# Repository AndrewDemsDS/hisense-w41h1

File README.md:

# Hisense AEH-W41H1: local A/C control with ESPHome

ESPHome firmware that takes the place of the ConnectLife cloud on a Hisense A/C with an
`AEH-W41H1` Wi-Fi module. It speaks the A/C's internal RS-485 bus and presents the unit to Home
Assistant as a native climate device, with no cloud.

> Not affiliated with, endorsed by, or supported by Hisense, Realtek or ESPHome. See
> [`NOTICE.md`](NOTICE.md). Reverse engineering of hardware you own, for interoperability. Do this
> at your own risk: a bad flash can brick the stock module (recoverable with a dump you took
> first).

**Documentation: [andrewdemsds.github.io/hisense-w41h1](https://andrewdemsds.github.io/hisense-w41h1/).**
The site is generated from [`docs/guide/`](docs/guide/), [`firmware/docs/`](firmware/docs/) and
[`reverse-engineering/docs/`](reverse-engineering/docs/). This README only points into it.

```
Home Assistant ── ESPHome native API over Wi-Fi ──► ESP32 board or stock module
                                                    (hisense_ac ESPHome component)
                                                           │ RS-485 (9600 8N1)
                                                           ▼
                                                    A/C mainboard
```

## What you get

- A climate entity in Home Assistant over the ESPHome API: mode (including auto), setpoint
  (16 to 32 °C), six fan settings, vertical swing, and Eco, Quiet, Turbo and Sleep as presets.
- Switches for the special modes, the panel display and the command beeper.
- Commands that are checked: the node compares each one with the unit's status and sends it
  again when the unit missed it.
- Temperatures, compressor frequency, a power and energy estimate, and bus diagnostics.
- Updates over Wi-Fi with ESPHome's own OTA.

What each entity is and its limits: [Everyday Control](docs/guide/Everyday-Control.md).

## Which hardware

One firmware, three kinds of hardware.

| Hardware | State |
|---|---|
| An ESP32 board (ESP32-C3 SuperMini or classic ESP32) with a 3.3 V RS-485 transceiver, in place of the module | recommended. On live units since 2026-08 |
| The stock module itself (Realtek RTL8710C), through ESPHome's LibreTiny platform | one module in an A/C since 2026-10-10. No rollback, and a SOIC-8 clip is the only recovery |
| Other ESPHome chips (ESP8266, RP2040) | example configs that compile. Never run |

The [User Guide](docs/guide/User-Guide.md) compares them and says which page to read next.

## The quickest path to a working unit

With an ESP32 board wired as in
[ESP32 Replacement Board](docs/guide/ESP32-Replacement-Build.md), and ESPHome 2026.10.2 installed
(`pipx install esphome==2026.10.2`):

```
git clone https://github.com/AndrewDemsDS/hisense-w41h1.git
cd hisense-w41h1/firmware/esphome
cp secrets.yaml.example secrets.yaml      # then fill in Wi-Fi, a hotspot password and an API key
esphome run w41h1-esp32c3.yaml            # ESP32-C3 SuperMini. Classic ESP32: w41h1.yaml
```

Home Assistant then discovers the node, and you adopt it with the API key. Do not wire a freshly
flashed board straight into the A/C: the guide brings it up in three stages. For local builds and
the bench there is a wrapper script, `python3 firmware/scripts/dev.py`
([Build, Flash and Test](docs/guide/Build-Flash-Test.md)).

> **Stock module: dump it first.** The only complete way back to what a module had on it is a
> whole-chip write, with a CH341A and a clip, of a dump taken before the first flash.

## Where everything is

| I want to | Read |
|---|---|
| choose the hardware and follow the route | [User Guide](docs/guide/User-Guide.md) |
| know the module and the 4-pin port | [Hardware and Wiring](docs/guide/Hardware-and-Wiring.md) |
| install the tools and fill in the secrets | [Build Environment](docs/guide/ESP32-Build-Environment.md) |
| add the node to Home Assistant, update it, pin a release | [ESPHome Firmware](docs/guide/ESPHome-Build.md) |
| run ESPHome on the stock module | [The Stock Module](docs/guide/Stock-Module-Build.md) |
| see every entity and read the diagnostics | [Entities and Diagnostics](docs/guide/Entities-and-Diagnostics.md) |
| fix something | [Troubleshooting and FAQ](docs/guide/FAQ-Gotchas.md), [Recovery and Reflash](docs/guide/Recovery-and-Reflash.md) |
| find my way around the code and the tests | [Repo Map and Build Pipeline](docs/guide/Repo-Map-and-Build-Pipeline.md), [Testing and QA](docs/guide/Testing-and-QA.md) |
| read the protocol | [`reverse-engineering/docs/03-rs485-ac-protocol.md`](reverse-engineering/docs/03-rs485-ac-protocol.md) |
| contribute, or report a security problem | [`CONTRIBUTING.md`](CONTRIBUTING.md), [`SECURITY.md`](SECURITY.md) |
| see what changed | [`CHANGELOG.md`](CHANGELOG.md) |

Once local control works, you can block the vendor module's way out to the internet:
[`reverse-engineering/docs/04-cloud-and-firewall.md`](reverse-engineering/docs/04-cloud-and-firewall.md).

## Matter firmware (retired)

Until 2026-10-12 this repository also shipped two Matter firmwares. Both are retired. The last
tree that has them is the signed tag
[`matter-final`](https://github.com/AndrewDemsDS/hisense-w41h1/tree/matter-final). A unit that
runs one keeps working and can be moved to ESPHome over the air:
[Matter Firmware (Retired)](docs/guide/Matter-Firmware-Retired.md).

## AI assistance

I built this with AI assistance across the code, reverse-engineering, and docs. Commits carry an
`Assisted-by: AI` trailer.

## License

Original code and docs: **MIT** ([`LICENSE`](LICENSE)). Third-party tools the build fetches and
what was adapted from them: [`NOTICE.md`](NOTICE.md).

Credits: the protocol work started from
[`pslawinski/esphome_airconintl`](https://github.com/pslawinski/esphome_airconintl) and
[`deiger/AirCon`](https://github.com/deiger/AirCon). What came from each is in
[`NOTICE.md`](NOTICE.md#acknowledgements-earlier-work-on-this-ac-bus).

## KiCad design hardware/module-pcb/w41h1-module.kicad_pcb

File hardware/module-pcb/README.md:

# Replacement module PCB

> **Rev C has not been fabricated.** Rev B was: five assembled boards from JLCPCB, ordered
> 2026-10-28, and one of them has run on an A/C unit since 2026-11-06 (bus link up, OTA works).
> Rev C is still a test board for the A/C units, not a fit for the stock module's bay: the bay's
> size is unmeasured, and the A/C header's dimensions are marked VERIFY below.

A test board for local control of the A/C: an ESP32-C3 module, a 3.3 V RS-485 transceiver and
the 4-pin A/C connector. It runs the same ESPHome firmware as the hand-wired ESP32-C3 build,
with the same pins, so `firmware/esphome/w41h1-esp32c3.yaml` applies unchanged. The matching
case is in [`../module-case`](../module-case).

## Rev C

Two things came out of putting a rev B board on a unit:

- No plug that fits the JST PH header matched the A/C's lead. The lead plugs into the stock
  module's own header, so rev C takes that header: `J1` is the 4-pin 2.0 mm side-entry
  header desoldered from the stock module (measured on 2026-11-06: 2.0 mm pitch, no plastic
  pegs), on a project footprint written by `scripts/place.py`. Its mating face sits on the board
  edge. How far the pin row sits behind that face (`J1_PIN_INSET`, 4.0 mm), the drill (0.9 mm)
  and the body size are placeholders marked `VERIFY` in `place.py` until they are measured on
  the stock module.
- The programming pads were awkward to use. `J2` is now a 2.54 mm pin header on the top side,
  so a standard jumper lead fits. The 1.27 mm pads on the bottom are gone, and the USB test pads
  stay.

Neither connector is assembled: both are marked not fitted, left out of the BOM and placement
files, and soldered in by hand. The board grew from 52 to 56 mm to make room for the header.
`place.py` also swaps the footprints on the board to match the schematic, so a footprint
change needs no step in the GUI.

Rev A was the size of the stock PCB (40 x 20.5 mm, estimated from the FCC photos) with parts on
both sides. Rev B traded the stock size for a lower assembly price: every assembled part is on
the top side.

## What is on it

| Block | Part | Notes |
|---|---|---|
| MCU | ESP32-C3-WROOM-02 | PCB antenna at the end away from the connector, over bare board |
| Supply | TLV62569DBV buck, 2.2 uH, 5 V to 3.3 V | the A/C port is rated 5 V at 450 mA, and a buck draws less from it than a linear regulator during Wi-Fi bursts |
| Bus | SP3485EN, SM712 TVS on A and B | DE and RE tied to one GPIO, 10 k pulldown on DE, 10 k pullup on RO |
| A/C port | 4-pin, 2.0 mm, side entry (`J1`) | the stock module's own header, desoldered and soldered in by hand; not assembled |
| Status LED | 0603 on GPIO8, lights when the pin is low | same as the SuperMini's LED |
| Programming | `J2` 2.54 mm pin header on top (GND, 3V3, EN, IO9, TX, RX, pin 1 at the board edge) and USB D-, D+, 5 V, GND test pads on the bottom | the header is not assembled |

## Pins

| Signal | GPIO | Goes to |
|---|---|---|
| Bus TX | 5 | transceiver DI |
| Bus RX | 6 | transceiver RO |
| Bus DE | 10 | transceiver DE and RE |
| Status LED | 8 | LED cathode |
| Boot | 9 | `J2` pin 4, 10 k pullup |
| UART0 TX, RX | 21, 20 | `J2` pins 5 and 6 |
| USB D-, D+ | 18, 19 | `TP1`, `TP2` |

`J1` follows the pinout in [Hardware and Wiring](../../docs/guide/Hardware-and-Wiring.md): pin 1 is
5 V, pins 2 and 3 are the RS-485 pair, pin 4 is ground. A and B are interchangeable on this bus:
if the link does not come up, swap them in the lead.

## Dimensions

| Dimension | Value |
|---|---|
| Board | 56 x 22 mm, 2 layers, 1.6 mm |
| Mounting holes | two, 2.2 mm (M2), 2.7 mm in from the connector end and from each long edge |
| A/C header `J1` | 4-pin, 2.0 mm pitch (measured on the stock module), mating face on the board edge, pin row 4.0 mm behind it, 0.9 mm drills. Inset, drill and body size are VERIFY |
| Programming header `J2` | 1x6, 2.54 mm, top side, 0.9 mm drills |
| Smallest drill | 0.3 mm |

All of them are constants at the top of `scripts/place.py`. Change the numbers and run it again:
it writes the A/C header footprint, puts the footprints the schematic names on the board,
places every footprint, redraws the outline and the keepouts and refills the ground pours. Run
it with `--unroute` when a change moves parts, then route again.

`place.py` also edits the module footprint: of its 13 thermal vias of 0.2 mm, four become
0.3 mm and the rest plain copper, because anything under 0.3 mm costs extra at JLCPCB. KiCad
reports that change as one "footprint differs from library" warning.

## Ordering at JLCPCB

`bash scripts/fab.sh`, then on JLCPCB's quote page: upload the gerber zip, keep the minimum via
hole at 0.3 mm and the 4-wire Kelvin test off, turn on assembly as Economic, top side, then upload
`fab/w41h1-module-bom.csv` and `fab/w41h1-module-cpl.csv`. All 15 BOM lines match JLCPCB's
library. `J1` and `J2` are in neither file: solder them in yourself.

The quote on 2026-10-14 for five assembled rev B boards was EUR 51.99 before shipping:

| Item | EUR |
|---|---|
| Bare boards | 3.57 |
| Assembly setup and stencil | 8.72 |
| Parts | 20.82 |
| Extended parts fee (six parts outside JLCPCB's basic library) | 13.77 |
| Machine and hand assembly, nitrogen reflow | 5.11 |

Shipping by DHL was about EUR 21 more. Prices change, so quote again before ordering. Rev C
already leaves the connectors off the order; swapping the diode, the inductor and the 453 k
resistor for basic library parts would cut it further.

## Files

- `w41h1-module.kicad_pro`, `.kicad_sch`, `.kicad_pcb`: the KiCad 10 project.
- `fp-lib-table`, `w41h1.pretty/`: the project footprint library, holding the A/C header
  footprint that `place.py` writes.
- `bom.csv`: the bill of materials with manufacturer and LCSC part numbers.
- `scripts/place.py`: the A/C header footprint, footprint swaps, placement, outline, keepouts,
  silkscreen labels, ground pours and the pre-routed connections, all derived from the
  dimensions above.
- `scripts/route.py`: runs Freerouting on the board and cleans up after it (track widths,
  stray vias, pour refill).
- `scripts/stitch.py`: joins the ground pour islands with vias after routing.
- `scripts/fab.sh`: runs ERC and DRC, then writes the fabrication files into `fab/`.
- `scripts/jlc_cpl.py`: turns KiCad's placement file into JLCPCB's column names.

## Fabrication files

```bash
bash scripts/fab.sh
```

It stops if ERC or DRC reports an error. Otherwise `fab/` (not tracked in git) holds:

| File | For |
|---|---|
| `w41h1-module-gerbers.zip` | the board order: two layers, 1.6 mm |
| `w41h1-module-bom.csv`, `w41h1-module-cpl.csv` | assembly: parts and placement, top side, without the two connectors |
| `w41h1-module-schematic.pdf` | reading the circuit without KiCad |
| `w41h1-module.step` | the 3D model the case is checked against |

## Regenerating the layout

```bash
python3 scripts/place.py --unroute     # footprint, swaps, place, pre-route, pour
python3 scripts/route.py               # Freerouting (jar path in FREEROUTING_JAR), then cleanup
python3 scripts/stitch.py              # join the ground islands
bash scripts/fab.sh
```

The regulator's connections, the module's supply link and three boxed-in ground pads are
pre-routed by `place.py`. The autorouter does the rest, and it gives a different result on
every run, so check that DRC reports no unconnected items each time. `route.py` prints its own
count after the import; the pour islands it includes are what `stitch.py` joins. Freerouting
2.5 does not count the pre-routed connections as routed and logs them as "unrouted" at the end:
that is expected. Nothing is routed by hand.

## What was checked

- ERC: no violations.
- DRC with schematic parity: no errors and no unconnected items. Two warnings remain, the
  module's antenna outline on the silkscreen crossing the board edge, plus the field notes
  below.
- The BOM has 15 lines and the placement file 23 parts, none of them `J1` or `J2`.
- The case ([`../module-case`](../module-case)) against the board's STEP: no overlap. The STEP
  leaves out the two not-fitted connectors, so that check does not see them.
- Pinouts and external parts against the manufacturers' datasheets, for the TLV62569DBV
  (pin order, 0.6 V feedback reference, 10 to 47 uF output capacitance), the
  ESP32-C3-WROOM-02 (pin table, pullups on GPIO2, GPIO8 and GPIO9, 10 k and 1 uF on EN,
  0.5 A supply) and the SP3485 (pin order, 3.3 V supply). The divider of 453 k over 100 k
  gives 3.32 V.
- The SM712 against its datasheet: pins 1 and 2 are the two lines, pin 3 is ground, and it
  clamps the +12 V to -7 V range RS-485 uses.
- The inductor (`L1`, FTC252012S2R2MGCA) against the maker's catalogue: 2.2 uH, 65 mOhm
  maximum, 2.7 A heating current and 3.3 A saturation current at worst, well above what this
  board draws.
- SPICE runs of the feedback divider, the EN delay and the decoupling networks pass.
- The gerbers hold every layer and both drill files.

## Before ordering

- Check the placement preview on JLCPCB's order page, part by part: it stayed blank in the
  browser used for the quote above, so part orientations have not been checked there. The
  placement file passes KiCad's rotations through unchanged.
- Measure the stock header before ordering: the distance from its mating face to the pin row
  (`J1_PIN_INSET`), its pin size (`J1_DRILL`) and its body (`J1_BODY`) are placeholders in
  `scripts/place.py`. Also confirm that its pin 1 is 5 V.
- Apart from the pre-routed parts, the routing came from an autorouter (Freerouting 2.5.0)
  with the cleanup in `route.py` and nothing by hand. The tracks under the module on the
  bottom side are longer than a hand layout would make them, which is harmless at 9600 baud.
- `J1` and `J2` are marked as not fitted. Solder them in yourself.
- Schematic parity lists 30 notes about fields (part number, description) that the footprints
  on the board do not carry. "Update PCB from Schematic" in KiCad copies them over.

## First power-up

Follow the staged bring-up in the
[ESP32 replacement guide](../../docs/guide/ESP32-Replacement-Build.md): flash and test on the
bench first, then connect only A and B to the unit, and power the board from the A/C port
last. Erase the module's flash before the first flash. The `PROG` header is labelled on the
top: hold IO9 low while EN rises to enter the bootloader over UART0, or use the USB pads on
the bottom.

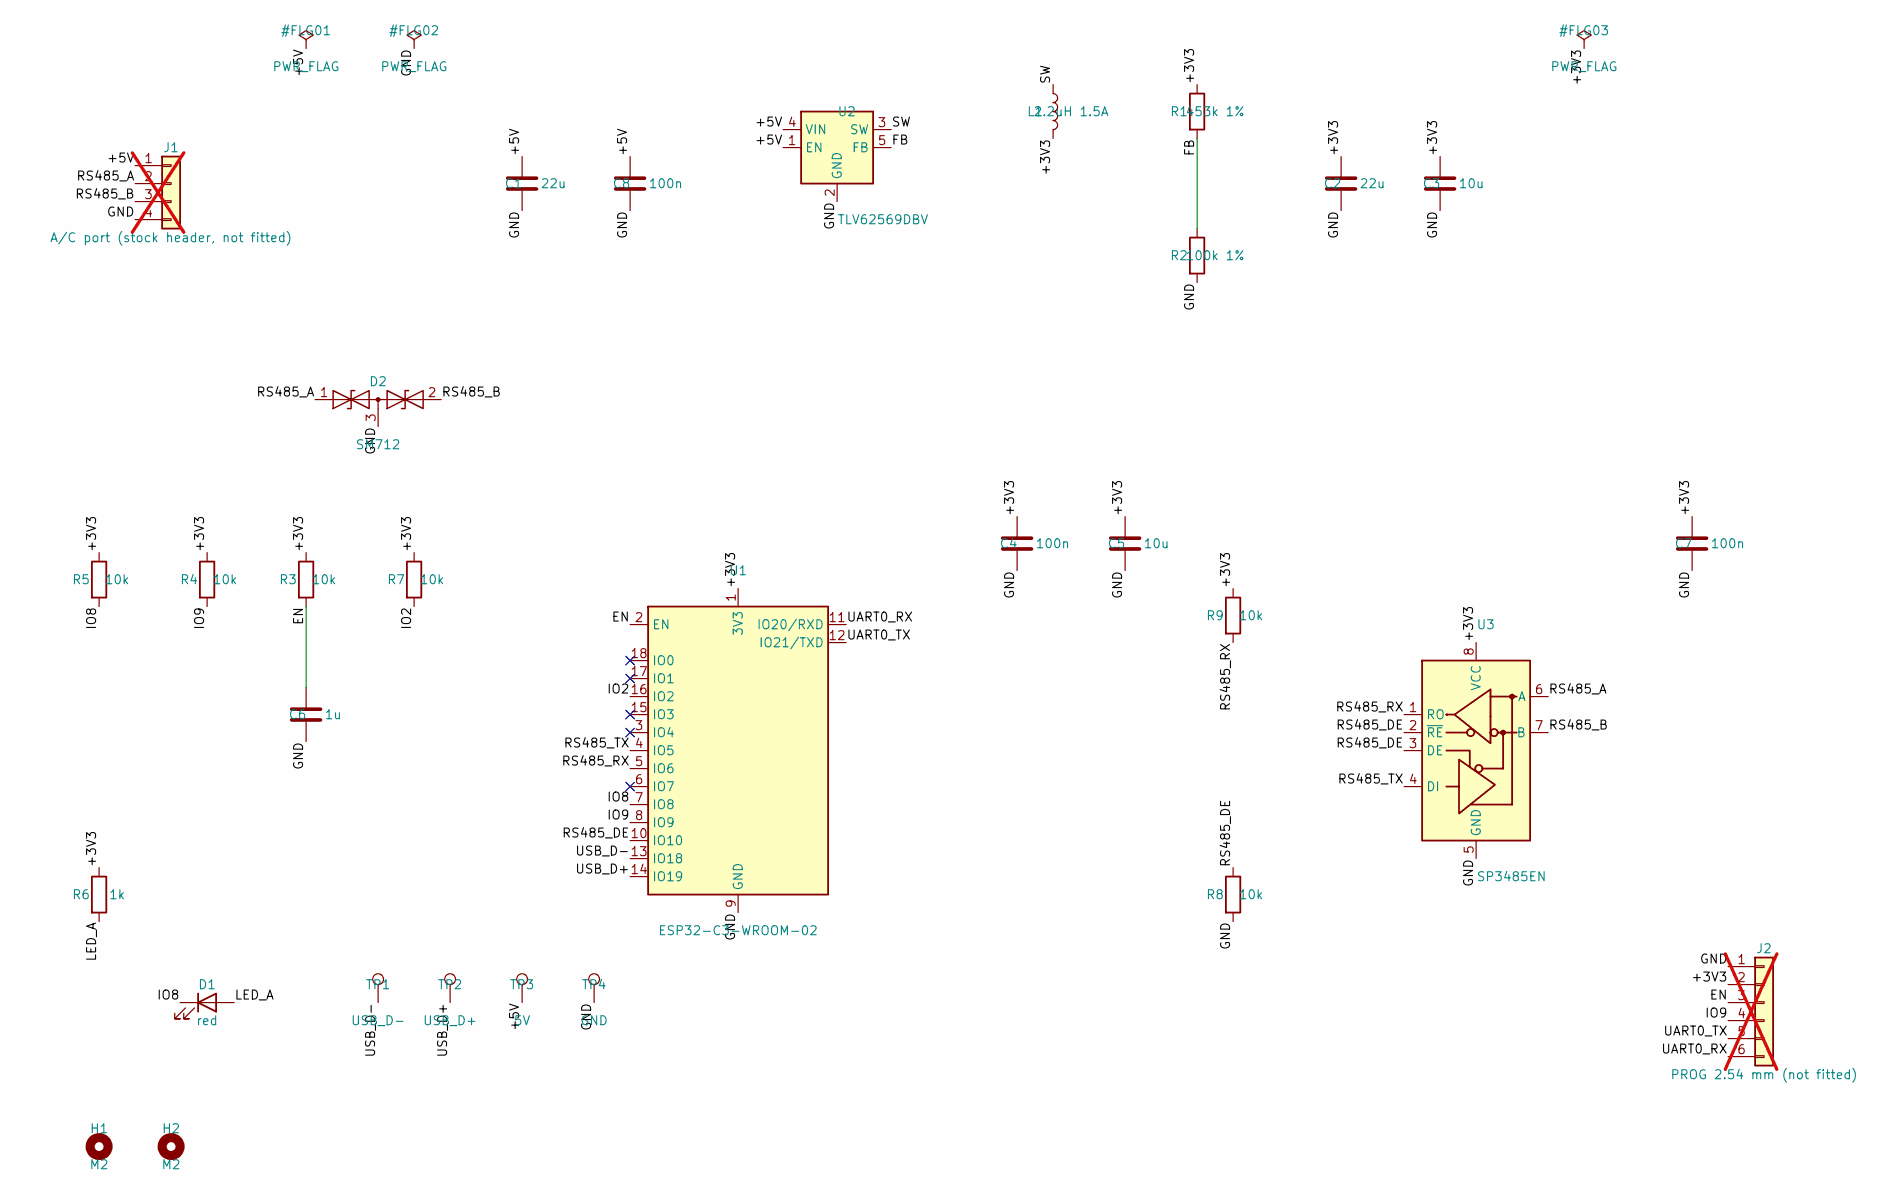
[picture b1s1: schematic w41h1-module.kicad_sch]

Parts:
C1, C2: 22u; C_0805_2012Metric; MPN CL21A226MAQNNNE; LCSC C45783
C3: 10u; C_0805_2012Metric; MPN CL21A106KAYNNNE; LCSC C15850
C4, C7, C8: 100n; C_0603_1608Metric; MPN CC0603KRX7R9BB104; LCSC C14663
C5: 10u; C_0603_1608Metric; MPN CL10A106KP8NNNC; LCSC C19702
C6: 1u; C_0603_1608Metric; MPN CL10A105KB8NNNC; LCSC C15849
D1: red; LED_0603_1608Metric; MPN KT-0603R; LCSC C2286
D2: SM712; SOT-23; MPN SM712; LCSC C502564
H1, H2: M2; MountingHole_2.2mm_M2
J1: A/C port (stock header, not fitted); AC_Header_1x04_P2.00mm_Horizontal; not fitted
J2: PROG 2.54 mm (not fitted); PinHeader_1x06_P2.54mm_Vertical; not fitted
L1: 2.2uH 1.5A; L_1008_2520Metric; MPN FTC252012S2R2MGCA; LCSC C48888311
R1: 453k 1%; R_0603_1608Metric; MPN 0603WAF4533T5E; LCSC C25818
R2: 100k 1%; R_0603_1608Metric; MPN 0603WAF1003T5E; LCSC C25803
R3, R4, R5, R7, R8, R9: 10k; R_0603_1608Metric; MPN 0603WAF1002T5E; LCSC C25804
R6: 1k; R_0603_1608Metric; MPN 0603WAF1001T5E; LCSC C21190
TP1: USB_D-; TestPoint_Pad_D1.0mm
TP2: USB_D+; TestPoint_Pad_D1.0mm
TP3: 5V; TestPoint_Pad_D1.0mm
TP4: GND; TestPoint_Pad_D1.0mm
U1: ESP32-C3-WROOM-02; MPN ESP32-C3-WROOM-02-N4; LCSC C2934560
U2: TLV62569DBV; SOT-23-5; MPN TLV62569DBVR; LCSC C141836
U3: SP3485EN; SOIC-8_3.9x4.9mm_P1.27mm; MPN SP3485EN-L/TR; LCSC C8963

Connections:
/+3V3: C2.1, C3.1, C4.1, C5.1, C7.1, J2.2, L1.2, R1.1, R3.1, R4.1, R5.1, R6.1, R7.1, R9.1, U1.1 (3V3), U3.8 (VCC)
/+5V: C1.1, C8.1, J1.1, TP3.1, U2.1 (EN), U2.4 (VIN)
/EN: C6.1, J2.3, R3.2, U1.2 (EN)
/FB: R1.2, R2.1, U2.5 (FB)
/GND: C1.2, C2.2, C3.2, C4.2, C5.2, C6.2, C7.2, C8.2, D2.3 (common), J1.4, J2.1, R2.2, R8.2, TP4.1, U1.9 (GND), U1.19 (GND), U2.2 (GND), U3.5 (GND)
/IO2: R7.2, U1.16 (IO2)
/IO8: D1.1 (K), R5.2, U1.7 (IO8)
/IO9: J2.4, R4.2, U1.8 (IO9)
/LED_A: D1.2 (A), R6.2
/RS485_A: D2.1 (A1), J1.2, U3.6 (A)
/RS485_B: D2.2 (A2), J1.3, U3.7 (B)
/RS485_DE: R8.1, U1.10 (IO10), U3.2 (~RE), U3.3 (DE)
/RS485_RX: R9.2, U1.5 (IO6), U3.1 (RO)
/RS485_TX: U1.4 (IO5), U3.4 (DI)
/SW: L1.1, U2.3 (SW)
/UART0_RX: J2.6, U1.11 (IO20/RXD)
/UART0_TX: J2.5, U1.12 (IO21/TXD)
/USB_D+: TP2.1, U1.14 (IO19)
/USB_D-: TP1.1, U1.13 (IO18)

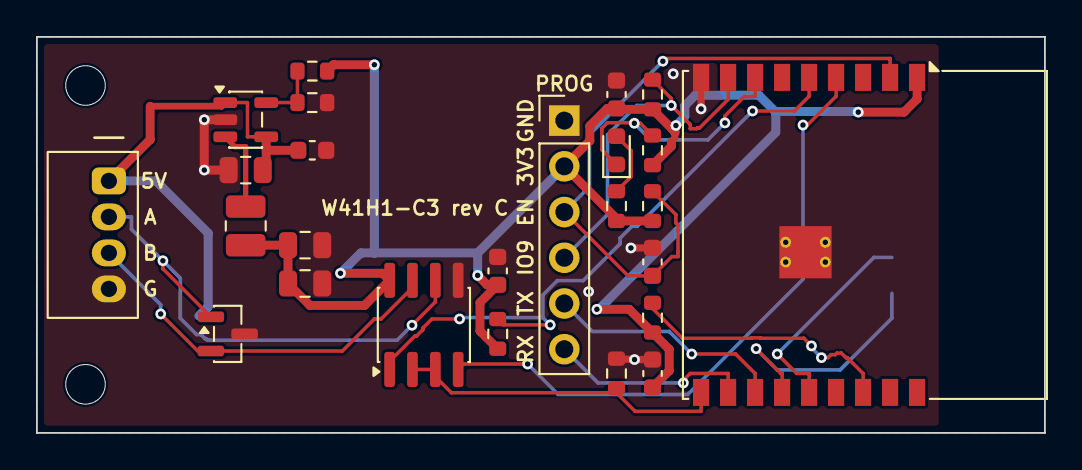
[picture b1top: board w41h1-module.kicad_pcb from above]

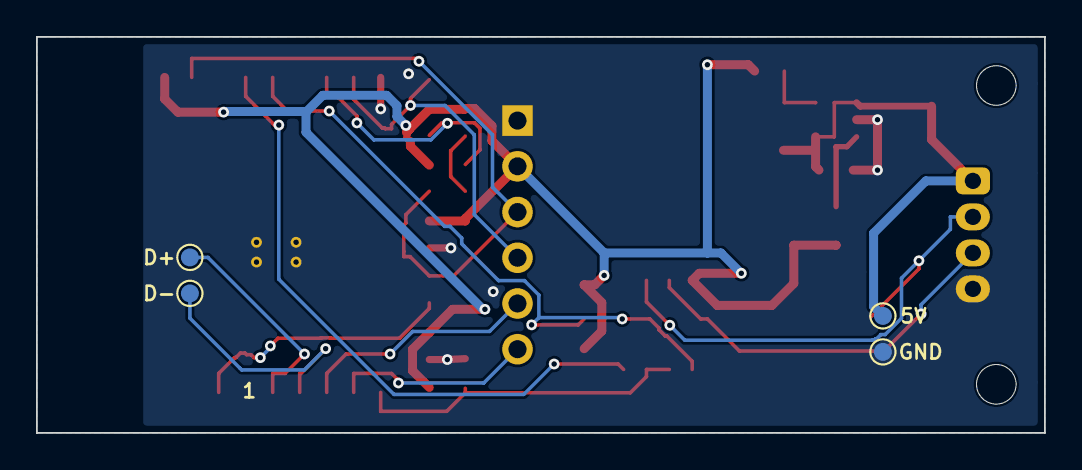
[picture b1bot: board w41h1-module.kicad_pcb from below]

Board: 2 copper layers, 56.0 x 22.0 mm, 31 parts (4 on the bottom side), 19 nets.

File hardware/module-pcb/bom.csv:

"Comment","Designator","Footprint","LCSC","MPN","Manufacturer"
"22u","C1,C2","Capacitor_SMD:C_0805_2012Metric","C45783","CL21A226MAQNNNE","Samsung"
"10u","C3","Capacitor_SMD:C_0805_2012Metric","C15850","CL21A106KAYNNNE","Samsung"
"100n","C4,C7,C8","Capacitor_SMD:C_0603_1608Metric","C14663","CC0603KRX7R9BB104","Yageo"
"10u","C5","Capacitor_SMD:C_0603_1608Metric","C19702","CL10A106KP8NNNC","Samsung"
"1u","C6","Capacitor_SMD:C_0603_1608Metric","C15849","CL10A105KB8NNNC","Samsung"
"red","D1","LED_SMD:LED_0603_1608Metric","C2286","KT-0603R","Hubei KENTO"
"SM712","D2","Package_TO_SOT_SMD:SOT-23","C502564","SM712","MDD"
"2.2uH 1.5A","L1","Inductor_SMD:L_1008_2520Metric","C48888311","FTC252012S2R2MGCA","cjiang"
"453k 1%","R1","Resistor_SMD:R_0603_1608Metric","C25818","0603WAF4533T5E","UNI-ROYAL"
"100k 1%","R2","Resistor_SMD:R_0603_1608Metric","C25803","0603WAF1003T5E","UNI-ROYAL"
"10k","R3,R4,R5,R7,R8,R9","Resistor_SMD:R_0603_1608Metric","C25804","0603WAF1002T5E","UNI-ROYAL"
"1k","R6","Resistor_SMD:R_0603_1608Metric","C21190","0603WAF1001T5E","UNI-ROYAL"
"ESP32-C3-WROOM-02","U1","RF_Module:ESP32-C3-WROOM-02","C2934560","ESP32-C3-WROOM-02-N4","Espressif"
"TLV62569DBV","U2","Package_TO_SOT_SMD:SOT-23-5","C141836","TLV62569DBVR","Texas Instruments"
"SP3485EN","U3","Package_SO:SOIC-8_3.9x4.9mm_P1.27mm","C8963","SP3485EN-L/TR","MaxLinear"
